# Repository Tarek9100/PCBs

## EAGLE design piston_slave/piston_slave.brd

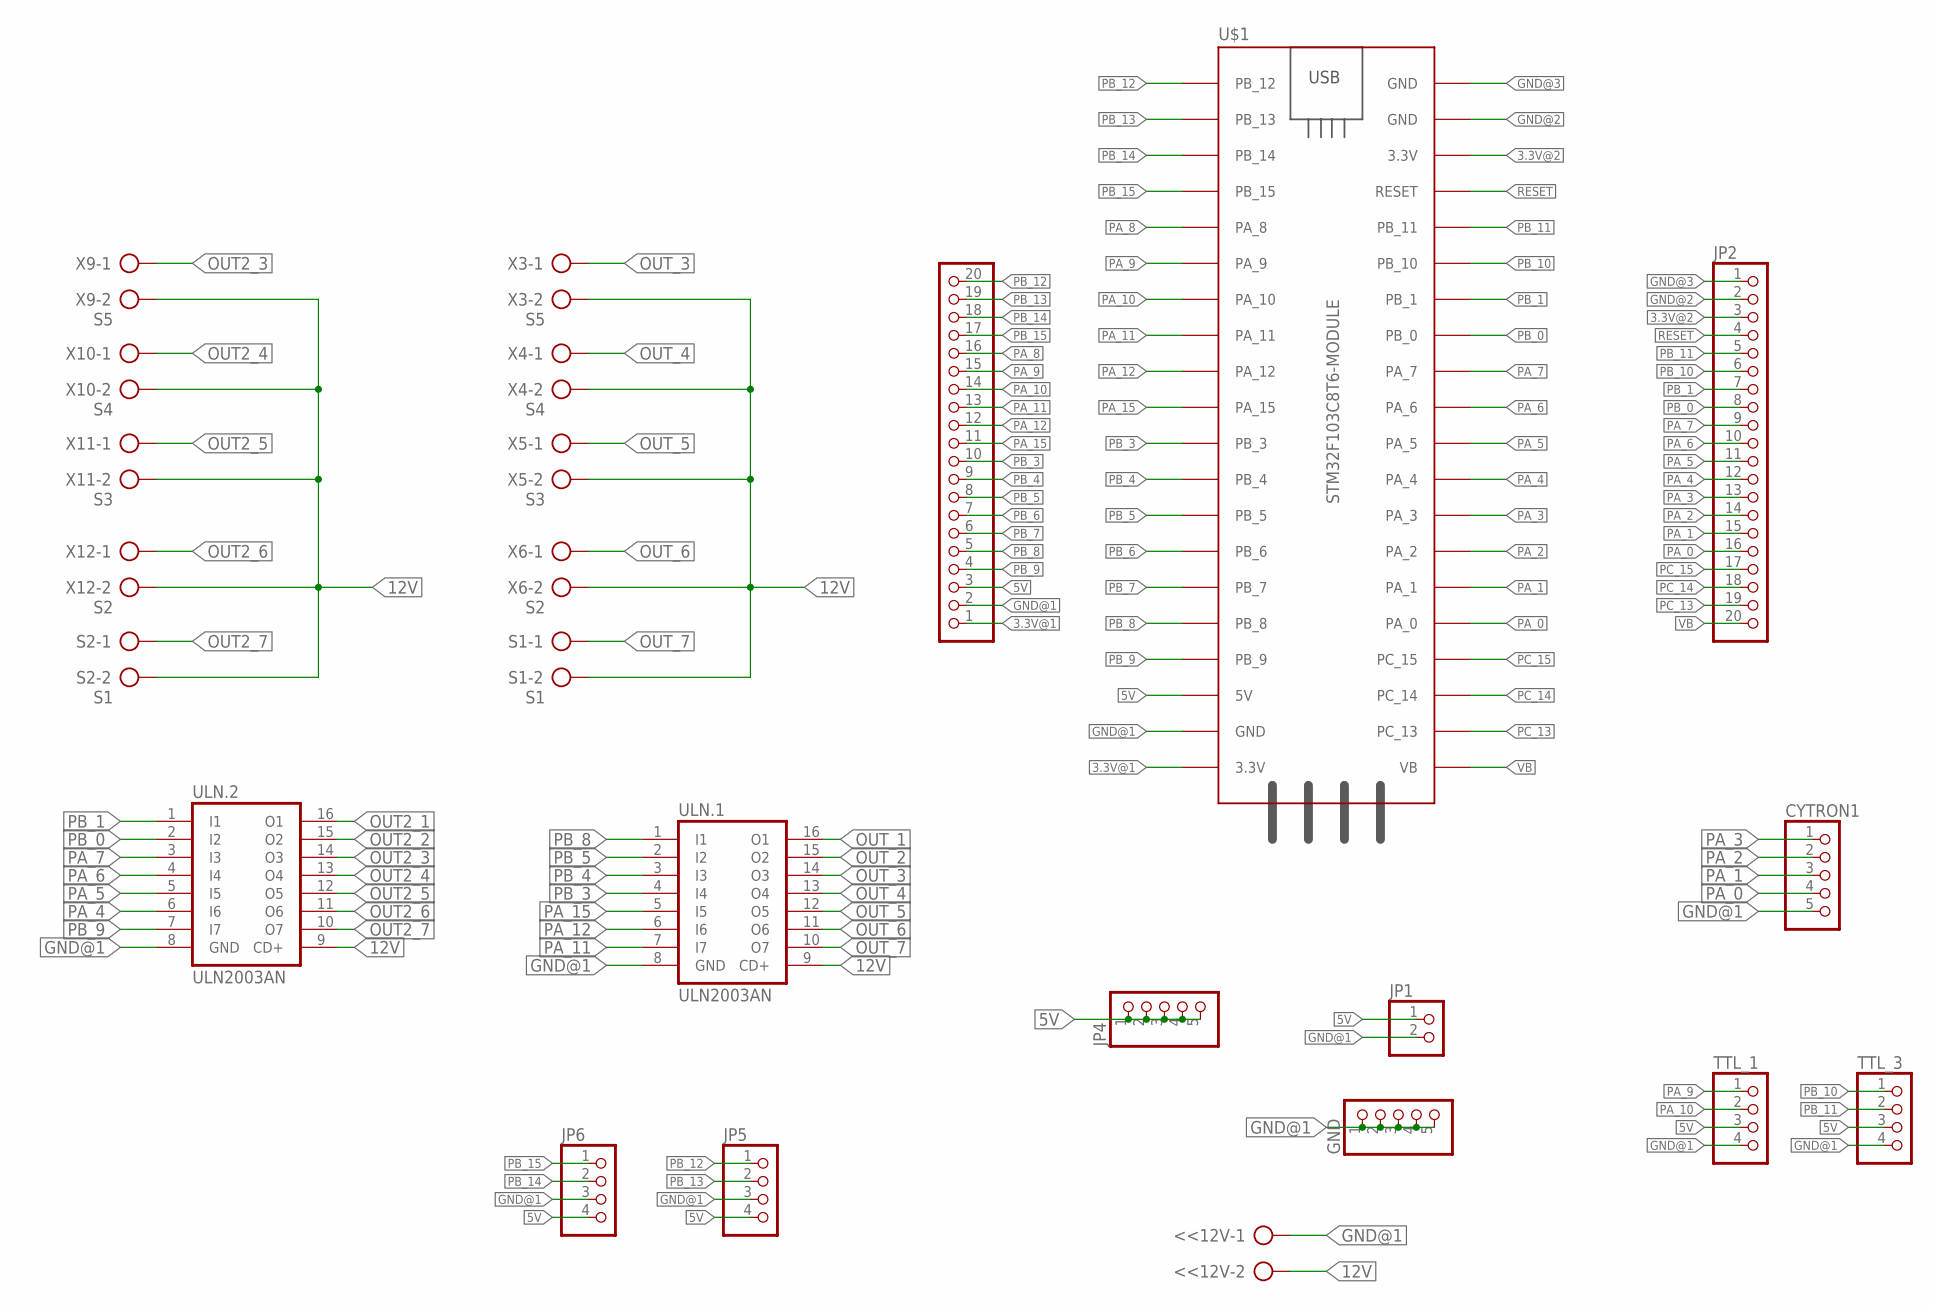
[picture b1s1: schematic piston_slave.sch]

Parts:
<<12V: AK300/2
CYTRON1: PINHD-5_DATA; DATA_5
GND: PINHD-1X5; 1X05
JP1: PINHD-2_DATA; 1X02_DATA
JP2, JP3: PINHD-1X20; 1X20
JP4: PINHD-1X5; 1X05
JP5, JP6: PINHD-4_DATA; 1X04_DATA
S1, S2: S1; AK300/2
TTL_1, TTL_3: PINHD-4_DATA; 1X04_DATA
U$1: STM32F103C8T6-MODULE
ULN.1, ULN.2: ULN2003AN; DIL16
X3, X9: S5; AK300/2
X4, X10: S4; AK300/2
X5, X11: S3; AK300/2
X6, X12: S2; AK300/2

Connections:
3.3V@1: JP3.1, U$1.3.3V_1 (3.3V)
3.3V@2: JP2.3, U$1.3.3V_2 (3.3V)
5V: JP1.1, JP3.3, JP4.1, JP4.2, JP4.3, JP4.4, JP4.5, JP5.4, JP6.4, TTL_1.3, TTL_3.3, U$1.5V
12V: <<12V.2, S1.2, S2.2, ULN.1.9 (CD+), ULN.2.9 (CD+), X3.2, X4.2, X5.2, X6.2, X9.2, X10.2, X11.2, X12.2
GND@1: <<12V.1, CYTRON1.5, GND.1, GND.2, GND.3, GND.4, GND.5, JP1.2, JP3.2, JP5.3, JP6.3, TTL_1.4, TTL_3.4, U$1.GND_1 (GND), ULN.1.8 (GND), ULN.2.8 (GND)
GND@2: JP2.2, U$1.GND_2 (GND)
GND@3: JP2.1, U$1.GND_3 (GND)
OUT2_1: ULN.2.16 (O1)
OUT2_2: ULN.2.15 (O2)
OUT2_3: ULN.2.14 (O3), X9.1
OUT2_4: ULN.2.13 (O4), X10.1
OUT2_5: ULN.2.12 (O5), X11.1
OUT2_6: ULN.2.11 (O6), X12.1
OUT2_7: S2.1, ULN.2.10 (O7)
OUT_1: ULN.1.16 (O1)
OUT_2: ULN.1.15 (O2)
OUT_3: ULN.1.14 (O3), X3.1
OUT_4: ULN.1.13 (O4), X4.1
OUT_5: ULN.1.12 (O5), X5.1
OUT_6: ULN.1.11 (O6), X6.1
OUT_7: S1.1, ULN.1.10 (O7)
PA_0: CYTRON1.4, JP2.16, U$1.PA_0
PA_1: CYTRON1.3, JP2.15, U$1.PA_1
PA_2: CYTRON1.2, JP2.14, U$1.PA_2
PA_3: CYTRON1.1, JP2.13, U$1.PA_3
PA_4: JP2.12, U$1.PA_4, ULN.2.6 (I6)
PA_5: JP2.11, U$1.PA_5, ULN.2.5 (I5)
PA_6: JP2.10, U$1.PA_6, ULN.2.4 (I4)
PA_7: JP2.9, U$1.PA_7, ULN.2.3 (I3)
PA_8: JP3.16, U$1.PA_8
PA_9: JP3.15, TTL_1.1, U$1.PA_9
PA_10: JP3.14, TTL_1.2, U$1.PA_10
PA_11: JP3.13, U$1.PA_11, ULN.1.7 (I7)
PA_12: JP3.12, U$1.PA_12, ULN.1.6 (I6)
PA_15: JP3.11, U$1.PA_15, ULN.1.5 (I5)
PB_0: JP2.8, U$1.PB_0, ULN.2.2 (I2)
PB_1: JP2.7, U$1.PB_1, ULN.2.1 (I1)
PB_3: JP3.10, U$1.PB_3, ULN.1.4 (I4)
PB_4: JP3.9, U$1.PB_4, ULN.1.3 (I3)
PB_5: JP3.8, U$1.PB_5, ULN.1.2 (I2)
PB_6: JP3.7, U$1.PB_6
PB_7: JP3.6, U$1.PB_7
PB_8: JP3.5, U$1.PB_8, ULN.1.1 (I1)
PB_9: JP3.4, U$1.PB_9, ULN.2.7 (I7)
PB_10: JP2.6, TTL_3.1, U$1.PB_10
PB_11: JP2.5, TTL_3.2, U$1.PB_11
PB_12: JP3.20, JP5.1, U$1.PB_12
PB_13: JP3.19, JP5.2, U$1.PB_13
PB_14: JP3.18, JP6.2, U$1.PB_14
PB_15: JP3.17, JP6.1, U$1.PB_15
PC_13: JP2.19, U$1.PC_13
PC_14: JP2.18, U$1.PC_14
PC_15: JP2.17, U$1.PC_15
RESET: JP2.4, U$1.RESET
VB: JP2.20, U$1.VB

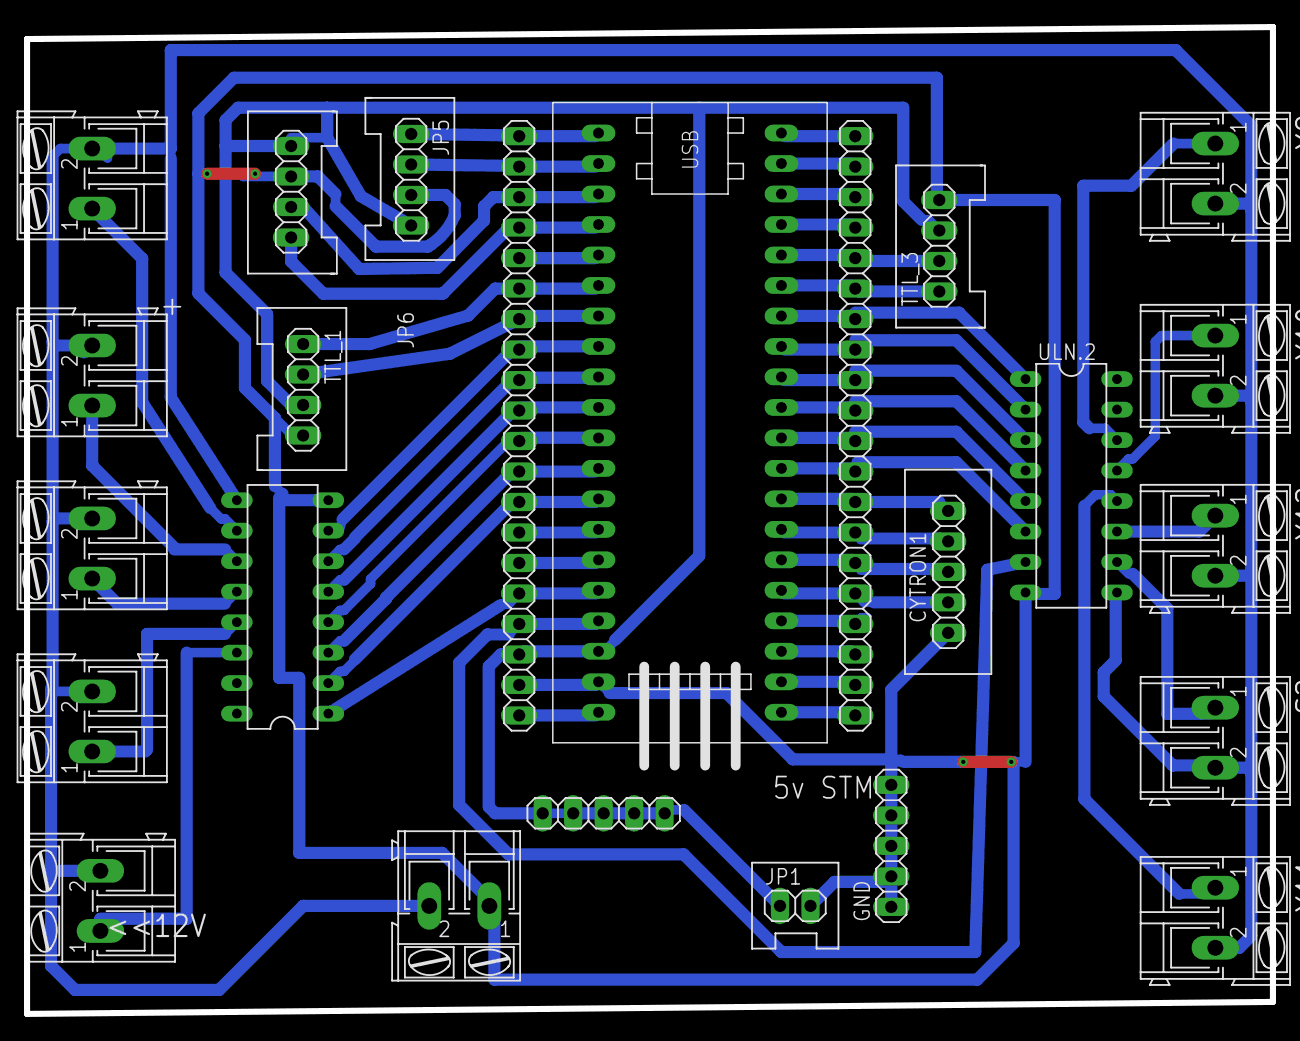
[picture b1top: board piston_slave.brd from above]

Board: 2 copper layers, 103.8 x 82.2 mm, 24 parts (0 on the bottom side), 51 nets.

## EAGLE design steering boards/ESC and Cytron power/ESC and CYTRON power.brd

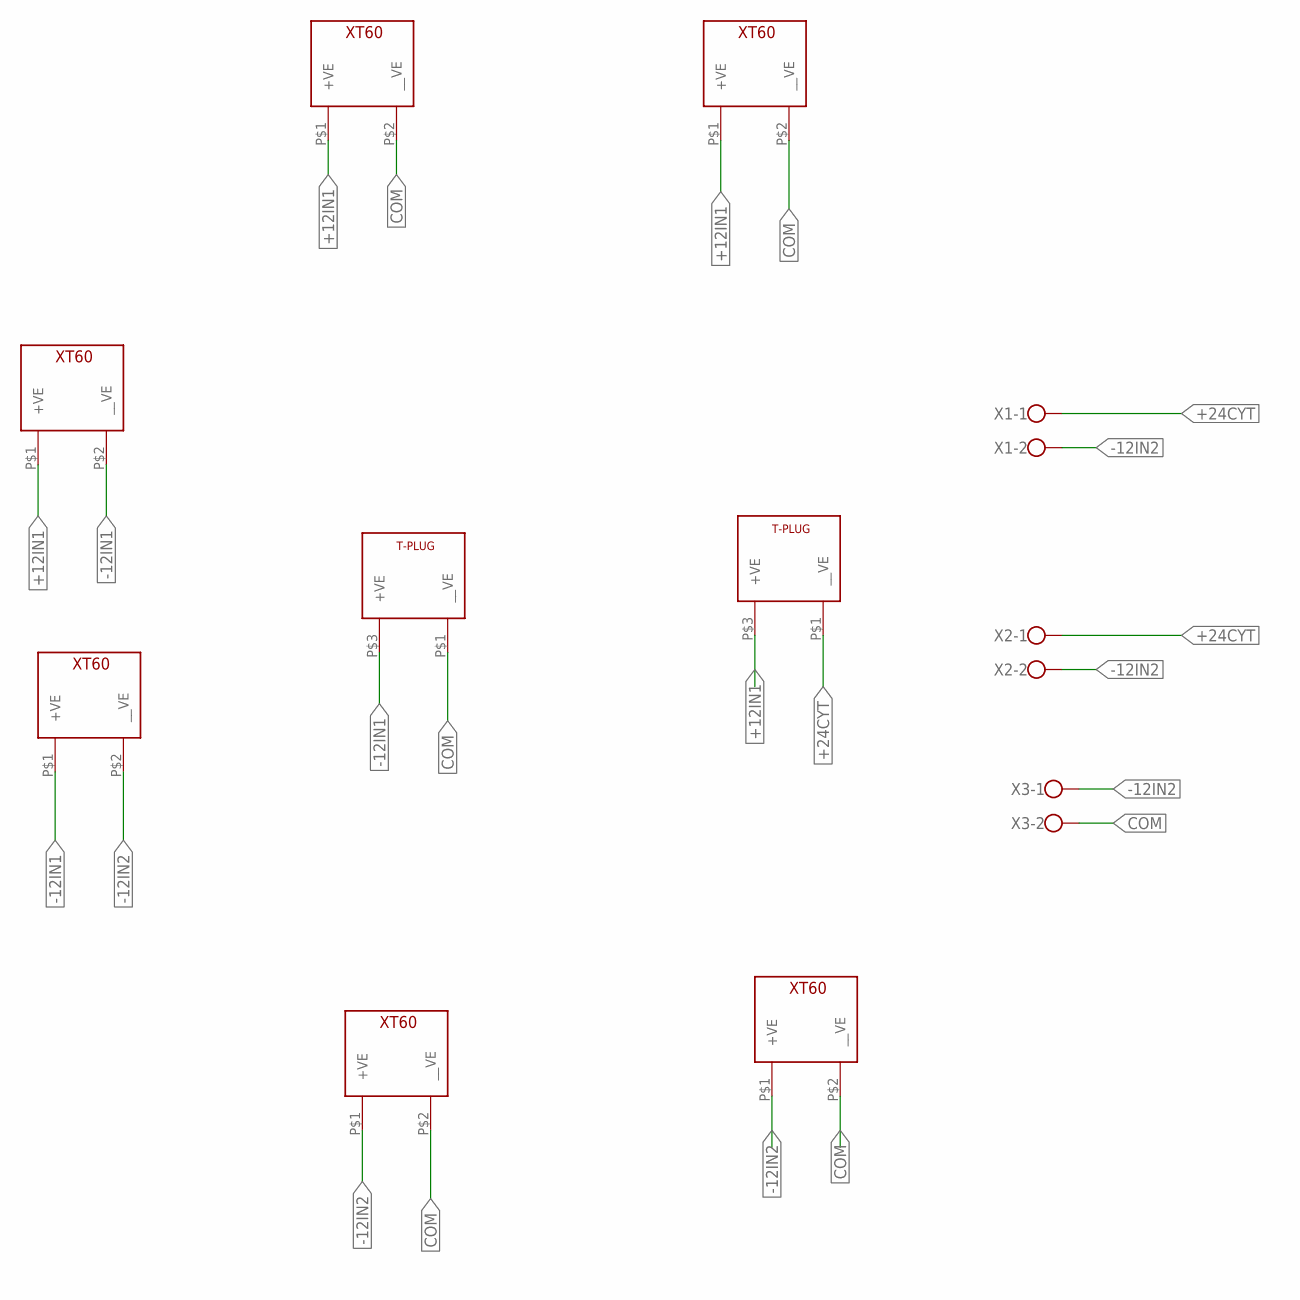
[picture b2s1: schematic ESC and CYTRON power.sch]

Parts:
BAT1, BAT2: XT60_CONNECTOR; XT60
CYT-SW: T_CONNECTOR; T-PLUG
ESC-B1, ESC-B2: XT60_CONNECTOR; XT60
ESC-SW: T_CONNECTOR; T-PLUG
ESC-T1, ESC-T2: XT60_CONNECTOR; XT60
X1, X2, X3: ROSTA.POWER; W239-302

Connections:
+12IN1: BAT1.P$1 (+VE), CYT-SW.P$3 (+VE), ESC-T1.P$1 (+VE), ESC-T2.P$1 (+VE)
+24CYT: CYT-SW.P$1 (__VE), X1.1, X2.1
-12IN1: BAT1.P$2 (__VE), BAT2.P$1 (+VE), ESC-SW.P$3 (+VE)
-12IN2: BAT2.P$2 (__VE), ESC-B1.P$1 (+VE), ESC-B2.P$1 (+VE), X1.2, X2.2, X3.1
COM: ESC-B1.P$2 (__VE), ESC-B2.P$2 (__VE), ESC-SW.P$1 (__VE), ESC-T1.P$2 (__VE), ESC-T2.P$2 (__VE), X3.2

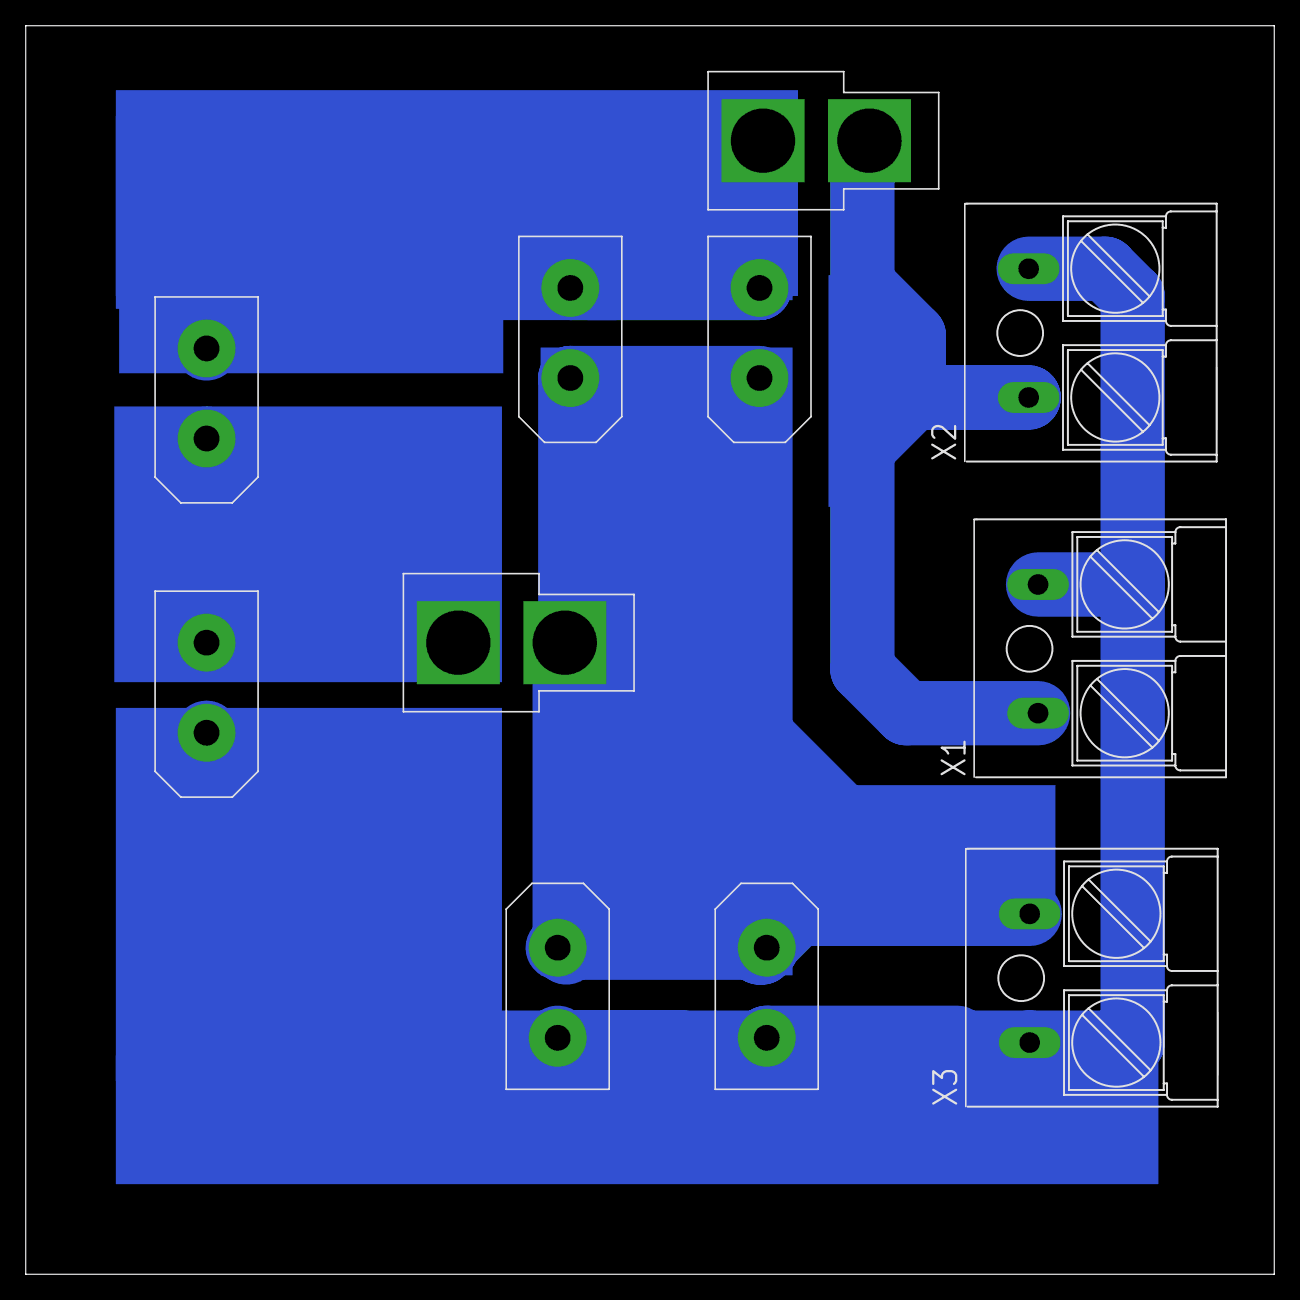
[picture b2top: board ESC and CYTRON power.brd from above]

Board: 2 copper layers, 97.0 x 97.0 mm, 11 parts (0 on the bottom side), 5 nets.

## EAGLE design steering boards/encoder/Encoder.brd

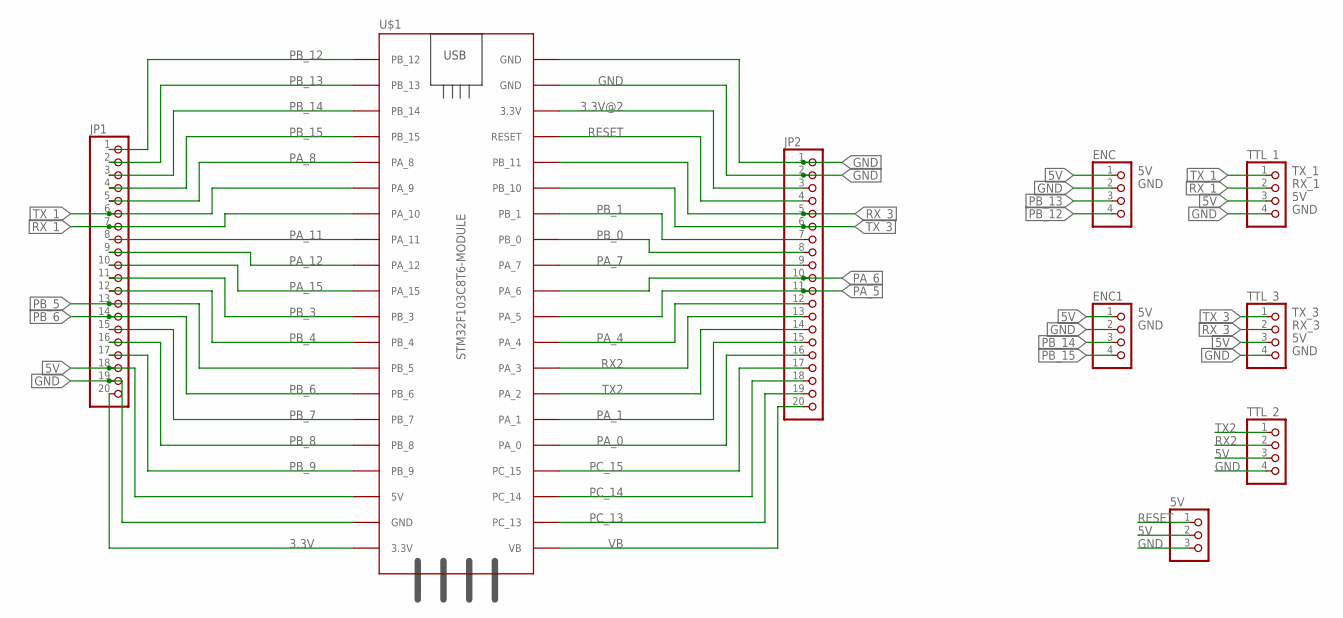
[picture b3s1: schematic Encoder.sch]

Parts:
5V: PINHD-3_DATA; 1X03_DATA
ENC, ENC1: PINHD-4_DATA; 1X04_DATA
JP1, JP2: PINHD-1X20; 1X20
TTL_1, TTL_2, TTL_3: PINHD-4_DATA; 1X04_DATA
U$1: STM32F103C8T6-MODULE

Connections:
3.3V: JP1.20, U$1.3.3V_1 (3.3V)
3.3V@2: JP2.3, U$1.3.3V_2 (3.3V)
5V: 5V.2, ENC.1, ENC1.1, JP1.18, TTL_1.3, TTL_2.3, TTL_3.3, U$1.5V
GND: 5V.3, ENC.2, ENC1.2, JP1.19, JP2.1, JP2.2, TTL_1.4, TTL_2.4, TTL_3.4, U$1.GND_1 (GND), U$1.GND_2 (GND), U$1.GND_3 (GND)
PA_0: JP2.16, U$1.PA_0
PA_1: JP2.15, U$1.PA_1
PA_4: JP2.12, U$1.PA_4
PA_5: JP2.11, U$1.PA_5
PA_6: JP2.10, U$1.PA_6
PA_7: JP2.9, U$1.PA_7
PA_8: JP1.5, U$1.PA_8
PA_11: JP1.8, U$1.PA_11
PA_12: JP1.9, U$1.PA_12
PA_15: JP1.10, U$1.PA_15
PB_0: JP2.8, U$1.PB_0
PB_1: JP2.7, U$1.PB_1
PB_3: JP1.11, U$1.PB_3
PB_4: JP1.12, U$1.PB_4
PB_5: JP1.13, U$1.PB_5
PB_6: JP1.14, U$1.PB_6
PB_7: JP1.15, U$1.PB_7
PB_8: JP1.16, U$1.PB_8
PB_9: JP1.17, U$1.PB_9
PB_12: ENC.4, JP1.1, U$1.PB_12
PB_13: ENC.3, JP1.2, U$1.PB_13
PB_14: ENC1.3, JP1.3, U$1.PB_14
PB_15: ENC1.4, JP1.4, U$1.PB_15
PC_13: JP2.19, U$1.PC_13
PC_14: JP2.18, U$1.PC_14
PC_15: JP2.17, U$1.PC_15
RESET: 5V.1, JP2.4, U$1.RESET
RX2: JP2.13, TTL_2.2, U$1.PA_3
RX_1: JP1.7, TTL_1.2, U$1.PA_10
RX_3: JP2.5, TTL_3.2, U$1.PB_11
TX2: JP2.14, TTL_2.1, U$1.PA_2
TX_1: JP1.6, TTL_1.1, U$1.PA_9
TX_3: JP2.6, TTL_3.1, U$1.PB_10
VB: JP2.20, U$1.VB

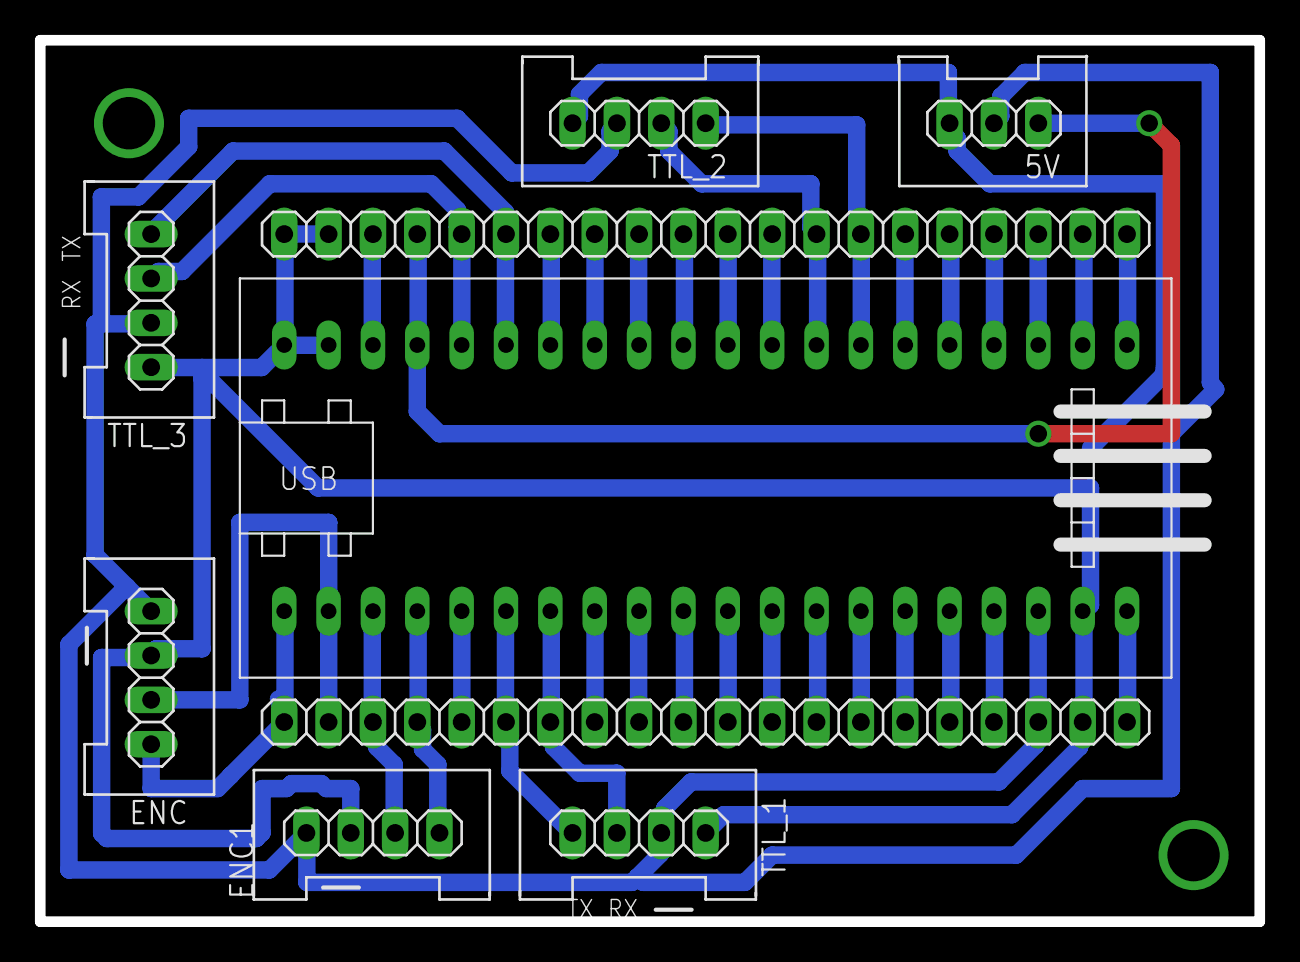
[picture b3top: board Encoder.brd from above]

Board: 2 copper layers, 69.8 x 50.5 mm, 9 parts (0 on the bottom side), 38 nets.

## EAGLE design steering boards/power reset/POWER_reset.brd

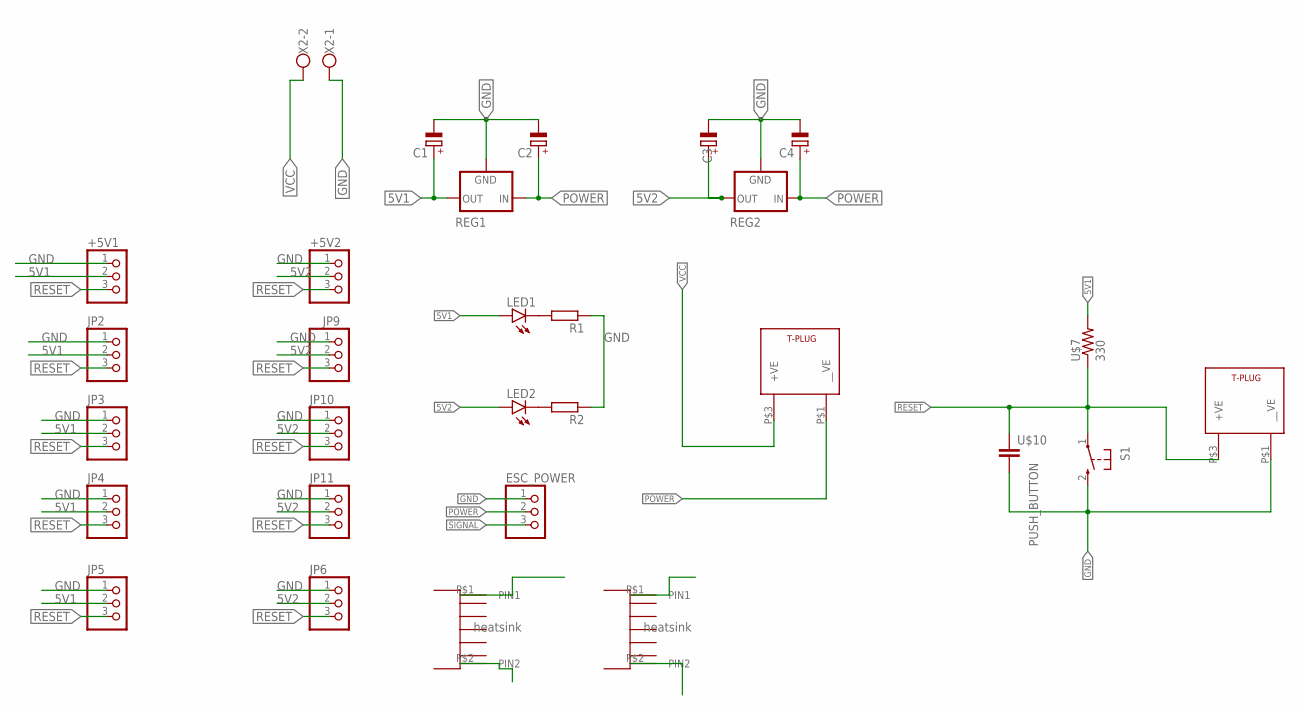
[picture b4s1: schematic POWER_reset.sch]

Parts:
+5V1, +5V2: PINHD-3_DATA; 1X03_DATA
C1, C2, C3, C4: CAP_POL; E3,5-8
ESC_POWER: PINHD-3_DATA; 1X03_DATA
JP2, JP3, JP4, JP5, JP6, JP9, JP10, JP11: PINHD-3_DATA; 1X03_DATA
LED1, LED2: LED5MM
R1, R2: R-EU_0204/7; 0204/7
REG1, REG2: 78XXS
S1: PUSH_BUTTON; B3F-10XX
U$1, U$2: HEAT-SINK; HEAT_SINK
U$3, U$4: T_CONNECTOR; T-PLUG
U$7: 330; 0204/7
U$10: CAPACITOR; C025-025X050
X2: ROSTA.POWER; W239-302

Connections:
5V1: +5V1.2, C1.+, JP2.2, JP3.2, JP4.2, JP5.2, LED1.A, REG1.OUT, U$7.2
5V2: +5V2.2, C3.+, JP6.2, JP9.2, JP10.2, JP11.2, LED2.A, REG2.OUT
GND: +5V1.1, +5V2.1, C1.-, C2.-, C3.-, C4.-, ESC_POWER.1, JP2.1, JP3.1, JP4.1, JP5.1, JP6.1, JP9.1, JP10.1, JP11.1, R1.1, R2.1, REG1.GND, REG2.GND, S1.2 (S), U$3.P$1 (__VE), U$10.2, X2.1
unnamed: LED1.K (C), R1.2
unnamed: LED2.K (C), R2.2
POWER: C2.+, C4.+, ESC_POWER.2, REG1.IN, REG2.IN, U$4.P$1 (__VE)
RESET: +5V1.3, +5V2.3, JP2.3, JP3.3, JP4.3, JP5.3, JP6.3, JP9.3, JP10.3, JP11.3, S1.1, U$3.P$3 (+VE), U$7.1, U$10.1
SIGNAL: ESC_POWER.3
VCC: U$4.P$3 (+VE), X2.2

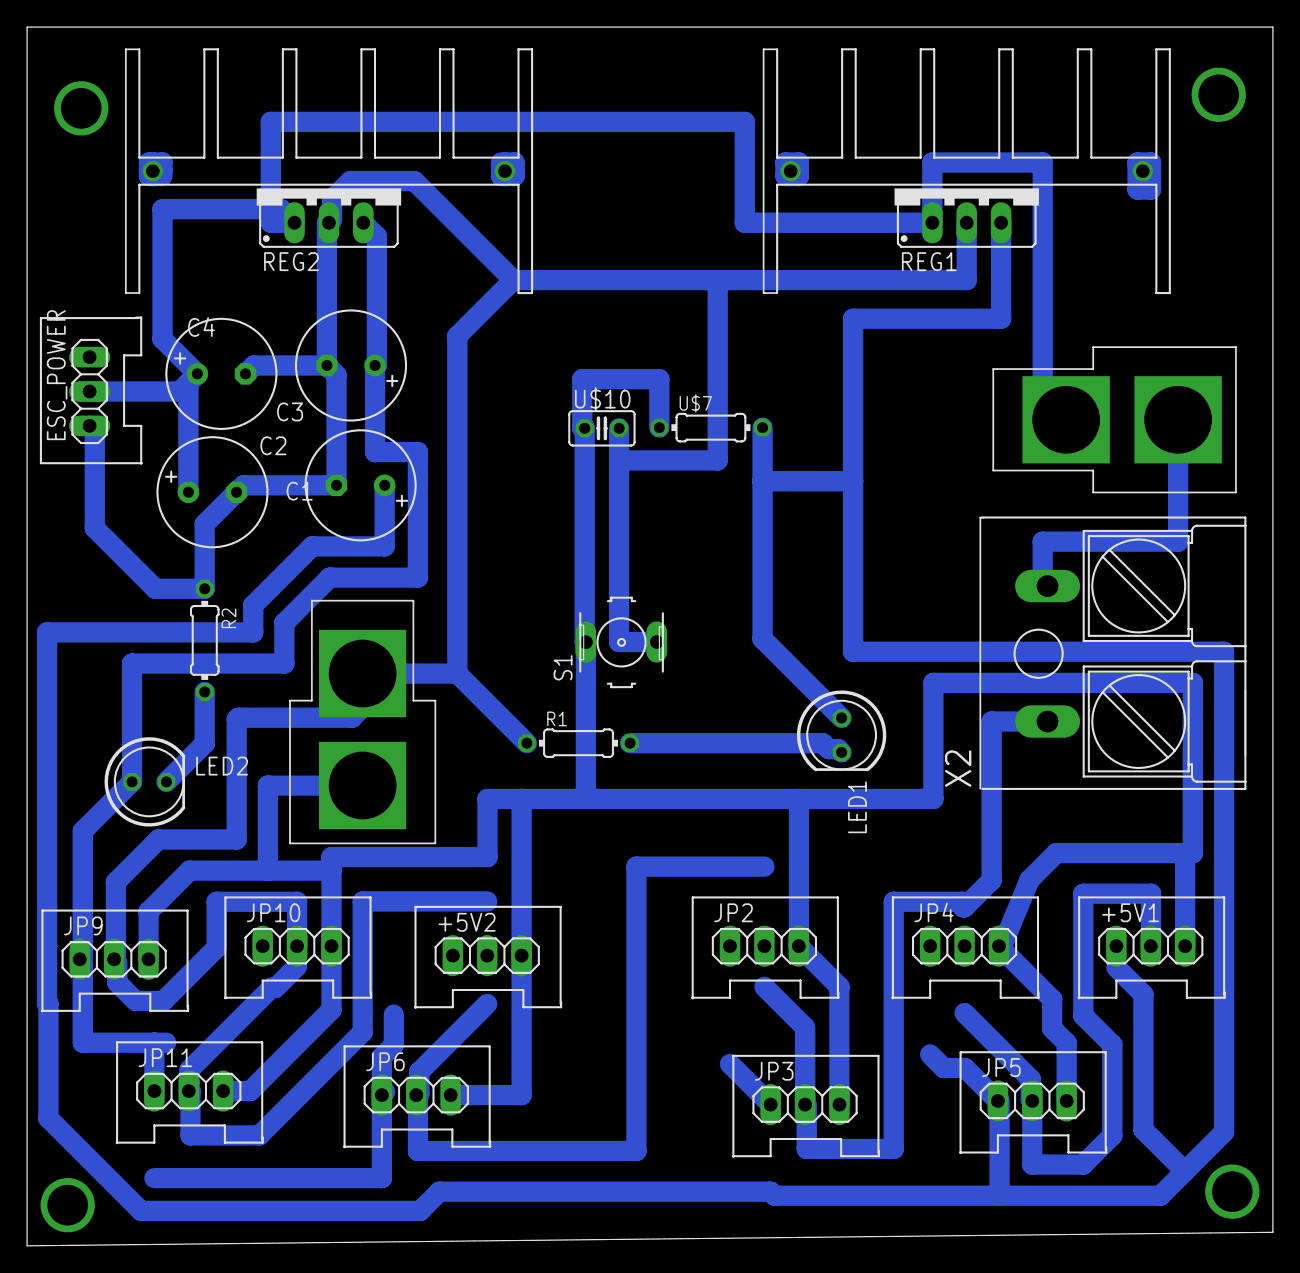
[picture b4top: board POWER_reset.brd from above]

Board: 2 copper layers, 92.0 x 90.0 mm, 29 parts (0 on the bottom side), 8 nets.
